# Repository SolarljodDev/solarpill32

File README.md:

# SolarPill32

A small, STM32-pin-compatible development/breakout board built around the
**CH32V303CBT6** (WCH, RISC-V32, LQFP-48). Footprint and pinout follow the
classic "blue pill / black pill" layout used by STM32F103C8T6 boards, so it
can be used as a drop-in RISC-V alternative in existing STM32 blue/black pill
projects and carriers.

## Board

- MCU: CH32V303CBT6, LQFP-48, 7x7 mm, 0.5 mm pitch (custom footprint
  `LQFP-48_7x7mm_P0.5mm.kicad_mod` included, as it's not in stock KiCad
  libraries).
- 4-layer PCB: top/bottom signal layers plus dedicated GND and 3V3 inner
  planes.
- Designed in KiCad 9.

## Repository contents

| Path | Description |
|---|---|
| `ch32_v303cb.kicad_pro/.kicad_sch/.kicad_pcb` | Main board project (schematic, layout) |
| `filter.kicad_sch` | Hierarchical sheet: power supply filtering |
| `LQFP-48_7x7mm_P0.5mm.kicad_mod` | Custom footprint for the CH32V303CBT6 |
| `SW_conv/` | Secondary small PCB project: switching converter module |
| `gerber/` | Exported Gerber + drill files for fabrication |

Files that KiCad regenerates automatically (autosave backups, `.lck` lock
files, `fp-info-cache`, local `.kicad_prl` view-state files, editor history)
are intentionally excluded — see `.gitignore`.

## License

Hardware design files (schematics, PCB layout, footprints, Gerbers) in this
repository are licensed under the
[CERN Open Hardware Licence Version 2 - Strongly Reciprocal (CERN-OHL-S-2.0)](LICENSE).

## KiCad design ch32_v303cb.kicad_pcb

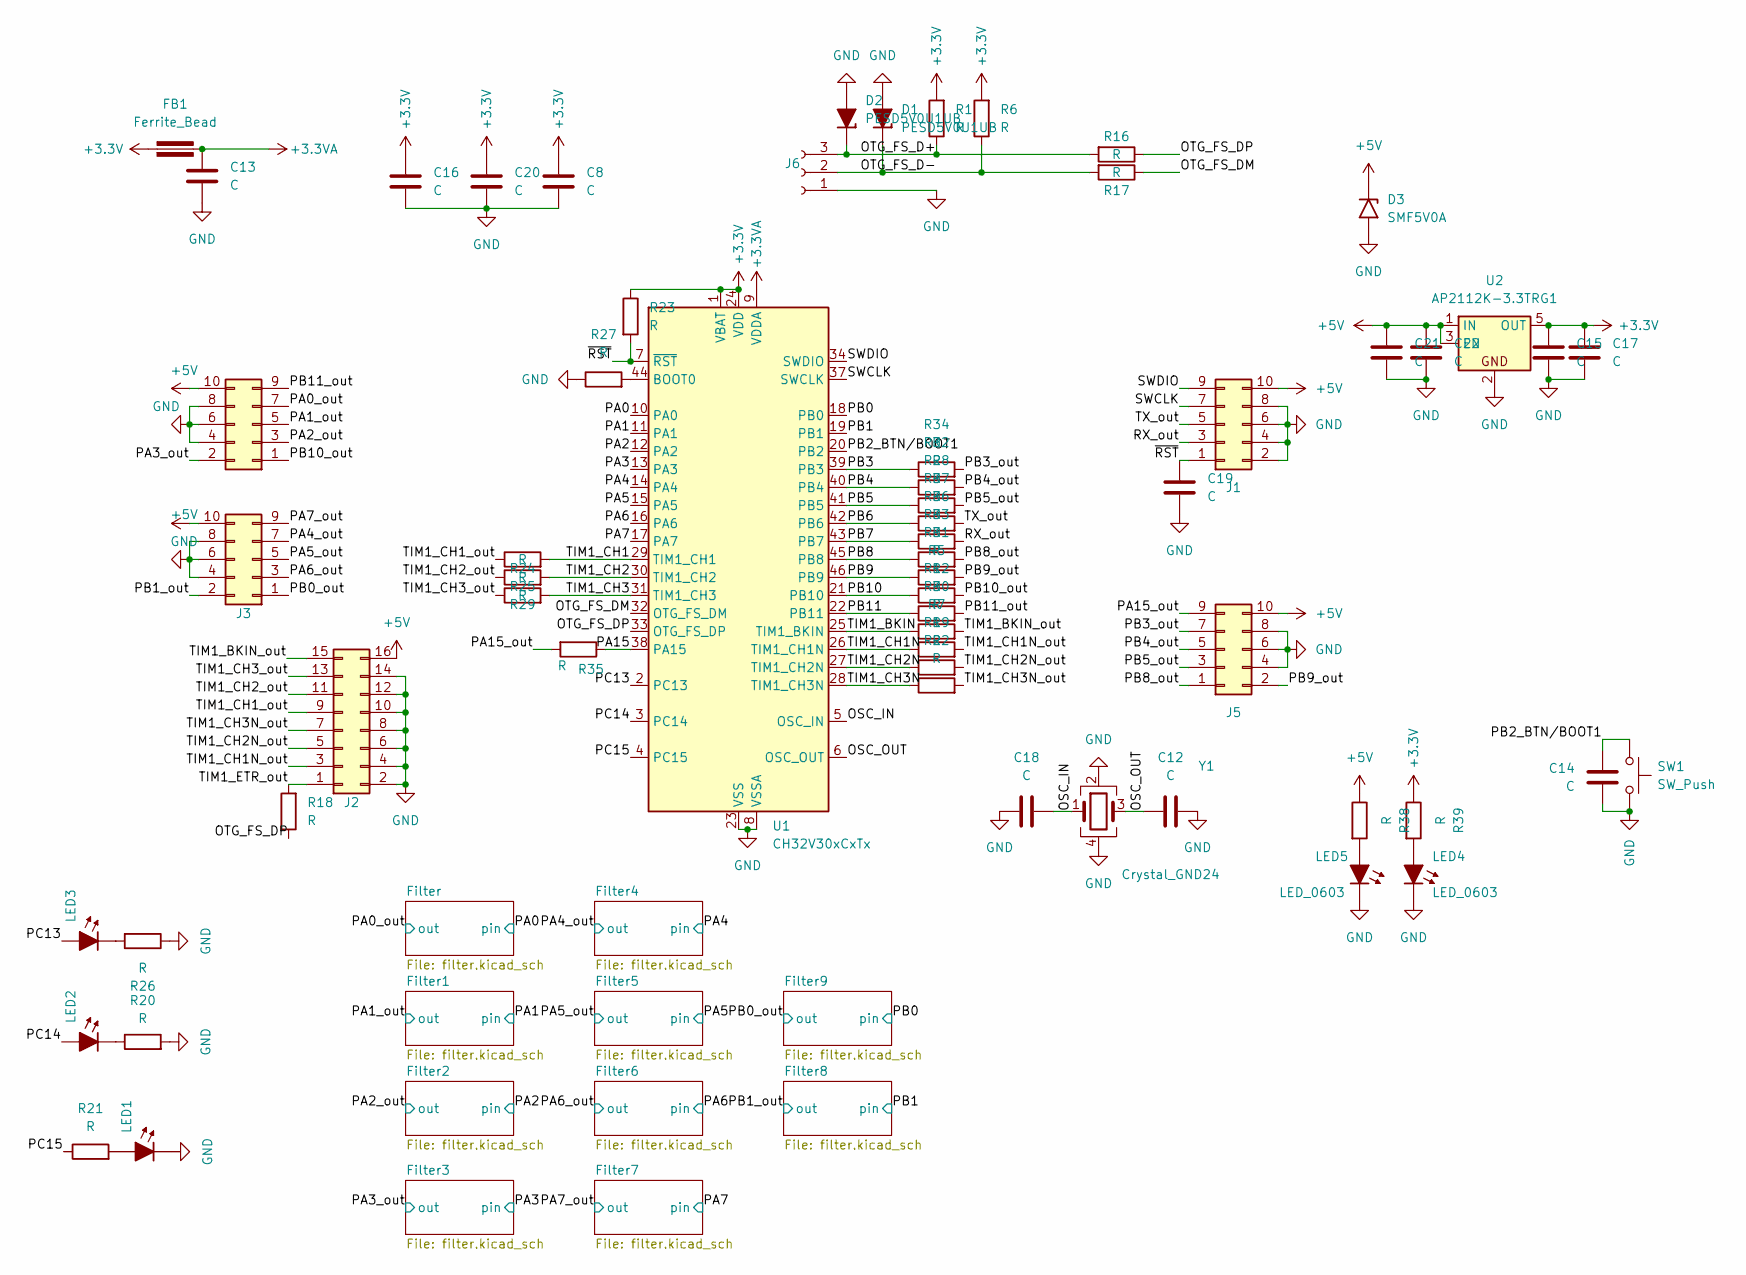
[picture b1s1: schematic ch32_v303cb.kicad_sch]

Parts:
C8, C12, C13, C14, C15, C16, C17, C18, C19, C20, C21, C22: C; C_0603
D1, D2: PESD5V0U1UB; D_SOD-523
D3: SMF5V0A; D_SMF
FB1: Ferrite_Bead; Ferrite_0603
J1, J3, J4, J5: Conn_02x05_Odd_Even; IDC-Header_2x5_P2.54mm_Horizontal_EDGE
J2: Conn_02x08_Odd_Even; IDC-Header_2x8_P2.54mm_Horizontal_EDGE
J6: Conn_01x02_Socket; PinSocket_1x03_P2.00mm_Vertical
LED1, LED2, LED3, LED4, LED5: LED_0603
R1, R5, R6, R7, R12, R16, R17, R18, R19, R20, R21, R22, R23, R24, R25, R26, R27, R28, R29, R30, R31, R32, R33, R34, R35, R36, R37, R38, R39: R; R_0603
SW1: SW_Push; SW_Push_1P1T_XKB_TS-1187A
U1: CH32V30xCxTx; LQFP-48_7x7mm_P0.5mm
U2: AP2112K-3.3TRG1; SOT-23-5
Y1: Crystal_GND24; Q3225

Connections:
+3.3VA: C13.1, FB1.2, U1.9 (VDDA)
+5V: C21.1, C22.1, D3.1 (A1), J1.10, J2.16, J3.10, J4.10, J5.10, R38.1, U2.1 (IN), U2.3 (EN)
/OSC_IN: C18.2, U1.5 (OSC_IN), Y1.1
/OSC_OUT: C12.1, U1.6 (OSC_OUT), Y1.3
/OTG_FS_D+: D2.1 (K), J6.3, R1.1, R16.2
/OTG_FS_D-: D1.1 (K), J6.2, R6.1, R17.2
/OTG_FS_DM: R17.1, U1.32 (OTG_FS_DM)
/OTG_FS_DP: R16.1, R18.1, U1.33 (OTG_FS_DP)
/PA0: U1.10 (PA0); also elsewhere on the board
/PA0_out: J4.7; also elsewhere on the board
/PA1: U1.11 (PA1); also elsewhere on the board
/PA1_out: J4.5; also elsewhere on the board
/PA2: U1.12 (PA2); also elsewhere on the board
/PA2_out: J4.3; also elsewhere on the board
/PA3: U1.13 (PA3); also elsewhere on the board
/PA3_out: J4.2; also elsewhere on the board
/PA4: U1.14 (PA4); also elsewhere on the board
/PA4_out: J3.7; also elsewhere on the board
/PA5: U1.15 (PA5); also elsewhere on the board
/PA5_out: J3.5; also elsewhere on the board
/PA6: U1.16 (PA6); also elsewhere on the board
/PA6_out: J3.3; also elsewhere on the board
/PA7: U1.17 (PA7); also elsewhere on the board
/PA7_out: J3.9; also elsewhere on the board
/PA15: R35.1, U1.38 (PA15)
/PA15_out: J5.9, R35.2
/PB0_out: J3.1; also elsewhere on the board
/PB1: U1.19 (PB1); also elsewhere on the board
/PB1_out: J3.2; also elsewhere on the board
/PB2_BTN/BOOT1: C14.1, SW1.1, U1.20 (PB2)
/PB3: R34.1, U1.39 (PB3)
/PB3_out: J5.7, R34.2
/PB4: R32.1, U1.40 (PB4)
/PB4_out: J5.5, R32.2
/PB5: R28.1, U1.41 (PB5)
/PB5_out: J5.3, R28.2
/PB6: R37.1, U1.42 (PB6)
/PB7: R36.1, U1.43 (PB7)
/PB8: R33.1, U1.45 (PB8)
/PB8_out: J5.1, R33.2
/PB9: R31.1, U1.46 (PB9)
/PB9_out: J5.2, R31.2
/PB10: R5.1, U1.21 (PB10)
/PB10_out: J4.1, R5.2
/PB11: R12.1, U1.22 (PB11)
/PB11_out: J4.9, R12.2
/PC13: LED3.2 (A), U1.2 (PC13)
/PC14: LED2.2 (A), U1.3 (PC14)
/PC15: R21.1, U1.4 (PC15)
/RX_out: J1.3, R36.2
/SWCLK: J1.7, U1.37 (SWCLK)
/SWDIO: J1.9, U1.34 (SWDIO)
/TIM1_BKIN: R30.1, U1.25 (TIM1_BKIN)
/TIM1_BKIN_out: J2.15, R30.2
/TIM1_CH1: R24.2, U1.29 (TIM1_CH1)
/TIM1_CH1N: R7.1, U1.26 (TIM1_CH1N)
/TIM1_CH1N_out: J2.3, R7.2
/TIM1_CH1_out: J2.9, R24.1
/TIM1_CH2: R25.2, U1.30 (TIM1_CH2)
/TIM1_CH2N: R19.1, U1.27 (TIM1_CH2N)
/TIM1_CH2N_out: J2.5, R19.2
/TIM1_CH2_out: J2.11, R25.1
/TIM1_CH3: R29.2, U1.31 (TIM1_CH3)
/TIM1_CH3N: R22.1, U1.28 (TIM1_CH3N)
/TIM1_CH3N_out: J2.7, R22.2
/TIM1_CH3_out: J2.13, R29.1
/TIM1_ETR_out: J2.1, R18.2
/TX_out: J1.5, R37.2
/~RST: C19.1, J1.1, R23.2, U1.7 (~RST)
GND: C8.2, C12.2, C13.2, C14.2, C15.2, C16.2, C17.2, C18.1, C19.2, C20.2, C21.2, C22.2, D1.2 (A), D2.2 (A), D3.2 (A2), J1.2, J1.4, J1.6, J1.8, J2.2, J2.4, J2.6, J2.8, J2.10, J2.12, J2.14, J3.4, J3.6, J3.8, J4.4, J4.6, J4.8, J5.4, J5.6, J5.8, J6.1, LED1.1 (K), LED4.1 (K), LED5.1 (K), R20.2, R26.1, R27.1, SW1.2, U1.8 (VSSA), U1.23 (VSS), U1.35 (VSS), U1.47 (VSS), U2.2, Y1.2, Y1.4; also elsewhere on the board
unnamed: LED5.2 (A), R38.2
unnamed: LED4.2 (A), R39.2
unnamed: LED3.1 (K), R26.2
unnamed: LED2.1 (K), R20.1
unnamed: LED1.2 (A), R21.2
unnamed: R27.2, U1.44 (BOOT0)

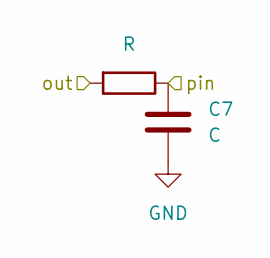
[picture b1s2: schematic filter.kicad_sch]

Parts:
C7: C; C_0603
R23: R; R_0603

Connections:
/~RST: R23.2; also elsewhere on the board
GND: C7.2; also elsewhere on the board

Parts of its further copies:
C1, C2, C3, C4, C5, C6, C9, C10, C11: C; C_0603
R2, R3, R4, R8, R9, R10, R11, R13, R14, R15: R; R_0603

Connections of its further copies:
/PA0: C4.1, R8.1; also elsewhere on the board
/PA0_out: R8.2; also elsewhere on the board
/PA1: C5.1, R9.1; also elsewhere on the board
/PA1_out: R9.2; also elsewhere on the board
/PA2: C1.1, R2.1; also elsewhere on the board
/PA2_out: R2.2; also elsewhere on the board
/PA3: C3.1, R13.1; also elsewhere on the board
/PA3_out: R13.2; also elsewhere on the board
/PA4: C2.1, R3.1; also elsewhere on the board
/PA4_out: R3.2; also elsewhere on the board
/PA5: C6.1, R10.1; also elsewhere on the board
/PA5_out: R10.2; also elsewhere on the board
/PA6: C10.1, R4.1; also elsewhere on the board
/PA6_out: R4.2; also elsewhere on the board
/PA7: C9.1, R15.1; also elsewhere on the board
/PA7_out: R15.2; also elsewhere on the board
/PB0_out: R11.2; also elsewhere on the board
/PB1: C11.1, R14.1; also elsewhere on the board
/PB1_out: R14.2; also elsewhere on the board
GND: C1.2, C2.2, C3.2, C4.2, C5.2, C6.2, C9.2, C10.2, C11.2; also elsewhere on the board

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
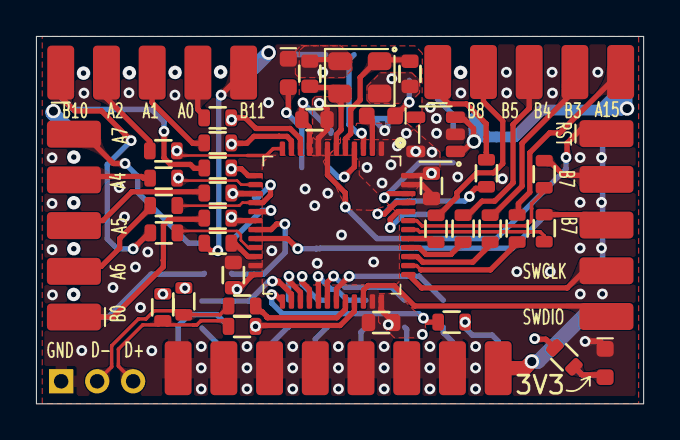
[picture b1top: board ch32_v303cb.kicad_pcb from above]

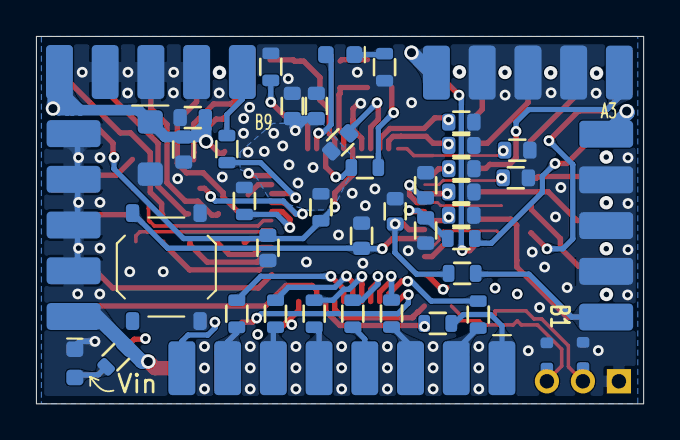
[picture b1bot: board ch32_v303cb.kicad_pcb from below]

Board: 4 copper layers, 33.7 x 20.4 mm, 80 parts (40 on the bottom side), 78 nets.
